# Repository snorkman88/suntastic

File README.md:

# DRAFT: Suntastic
An ultra low-power management board for meshtastic solar repeater devices.

## Overview

This repository contains the design proposal of a power management board for ultra low power embedded devices. The board features a solar charger circuit with Maximum Power Point Tracking (MPPT) for 5V solar panels, two DC-DC converters, a load switch control with adjustable hysteresis and an external Watchdog Timer.

## Why did I start this project?

### MPPT is a must
I recently started working with [Meshtastic](https://meshtastic.org/) and decided to deploy solar powered repeaters based on the WisBlock Core module that contains a RAK4631. So far it's been recommended to use this core module with any of the available base boards, however after inspecting [RAK's 19007](https://store.rakwireless.com/products/rak19007-wisblock-base-board-2nd-gen) base board, I noticed that the battery charging stage based on the [TP4054](https://www.laskakit.cz/user/related_files/tp4054.pdf) is not performing any kind of optimization to maximize the power available from the solar input.  

In contrast to linear chargers, MPPT chargers excel in extracting energy from solar panels under conditions such as partial shading, changing light angles, and fluctuating weather conditions. This adaptability is crucial for maximizing energy harvesting in real-world scenarios. By efficiently managing the charging process, MPPT helps prevent overcharging or undercharging of the accumulators in small IoT devices. This contributes to extending the overall lifespan of the battery, reducing the frequency of maintenance or battery replacement, and enhancing the device's reliability.  

### Reduce the current consumption of all the additional electronics
The recommended Wisblock base board RAK19007 contains extra electronics that are not really necessary once the RAK4631 core module has been correctly configured and flashed. This extra electronics however, do imply extra power consumption.  

As it's been empirically proven in [this thread](https://meshtastic.discourse.group/t/running-rak4631-without-the-rak19007/7021/21) once the RAK4631 core is flashed, it only needs a proper 3.3V power source to start working.  
However RAK actually recommends providing two voltage sources to the RAK4631, one that supplies power to the input of internal DC-DC buck converter and another 3.3V for the SX1262 chip. [SEE THIS POST](https://forum.rakwireless.com/t/rak4631-without-baseboard/10177/18)

### Supercapacitors as main energy storage
Another point that motivated the start of this project is the use of supercapacitors instead of conventional LiPo or LiFePo batteries. Whether supercapacitors are better than batteries for IoT devices depends on the specific requirements of the application. Here are some factors to consider:

1. Power Density:
Supercapacitors generally have higher power density than batteries. They can quickly charge and discharge, making them suitable for applications that require rapid bursts of energy. This can be advantageous in IoT devices that need to transmit data or perform periodic tasks quickly.

2. Cycle Life:
Supercapacitors often have a longer cycle life compared to batteries. Compared to batteries, they can withstand a large number of charge-discharge cycles without significant degradation in their structure even when being completely depleted and its output voltage drops down to 0V. This is beneficial for IoT devices that may need to operate for extended periods without maintenance.

3. Lifetime and Maintenance:
Supercapacitors can have a longer overall lifetime than batteries, as they do not suffer from the same degradation issues over time. They also require less maintenance since they do not have the same chemical processes that can lead to wear and tear in batteries.

4. Size and Weight:
Supercapacitors can be more compact and lighter than batteries, which is important for IoT devices with size and weight constraints. This is particularly relevant for small, portable devices or those with limited space.

5. Temperature Sensitivity:
Supercapacitors are known for their resilience to temperature variations, making them suitable for applications in harsh environments. This can be an advantage in IoT devices deployed in diverse environments where temperature fluctuations are common. Supercapacitors have a temperature range of operation og -40°C to 85°C or even higher in some cases.

6. Energy Density:
Batteries typically have higher energy density, meaning they can store more energy per unit of volume or weight. If the IoT device requires long periods of operation without recharging, a battery might be a more suitable choice.

In summary, the choice between supercapacitors and batteries for powering IoT devices depends on the specific requirements of the application. Supercapacitors may be a better choice for applications that require high power density, quick charge/discharge cycles, and long cycle life, while batteries may be preferable when higher energy density and longer operating periods without recharging are crucial. Each technology has its own strengths and limitations, and the decision should be based on the specific needs and constraints of the IoT deployment.  

### External Watchdog timers are sometimes needed
For IoT devices deployed in remote areas, the incorporation of an external watchdog timer becomes even more critical due to the challenges associated with limited accessibility and maintenance. Remote locations often entail harsh environmental conditions and restricted physical access, making it challenging to address issues promptly. The watchdog timer becomes a crucial asset in such scenarios as it autonomously monitors the device's operational state and intervenes in the case of failures. This capability ensures that even if a device experiences a software glitch or hardware malfunction, it can autonomously reset itself, mitigating potential downtime without requiring manual intervention.  

The reliability and self-correcting nature of an external watchdog timer contribute significantly to the overall resilience of IoT devices in remote deployments, enhancing their ability to function autonomously and maintain consistent operation in challenging and hard-to-reach environments.

## IMPORTANT
IMPORTANT: this board has been specifically thought to handle 5V solar panels and supercapacitors up to a voltage of 5.4V max.

## Table of Contents

- [Solar Charger Circuit](#solar-charger-circuit)
- [DC-DC Converters](#dc-dc-converters)
  - [Boost Converter](#boost-converter)
  - [Buck-Boost Converter](#buck-boost-converter)
- [UVLO - Schmitt Trigger Control](#schmitt-trigger-control)
- [External Watchdog timer](#watchdog-timer)
- [Monitoring of the voltage seen on the accumulator]()

## Solar Charger Circuit

The solar charger circuit is designed to efficiently charge an accumulator using 5V solar panels. It incorporates Maximum Power Point Tracking (MPPT) to optimize the energy harvesting from the solar panels.  

The [SPV1040](https://www.st.com/en/power-management/spv1040.html) device is a low power, low voltage, monolithic step-up converter with an input voltage range from 0.3 V to 5.5 V, capable of maximizing the energy generated by solar cells (or fuel cells), where low input voltage handling capability is extremely important. Thanks to the embedded MPPT algorithm, even under varying environmental conditions (such as irradiation, dirt, temperature) the SPV1040 offers maximum efficiency in terms of power harvested from the cells and transferred to the output. The device employs a voltage regulation loop, which fixes the charging battery voltage via a resistor divider.  

It is possible to set the maximum output current according to charging requirements by a sense resistor .

## DC-DC Converters

### Boost Converter

The first DC-DC converter that is presented is a boost converter responsible for powering the control stage and the input of the internal DC/DC converter present in the nRF52840.  
It is based on a [TPS61202](https://www.sparkfun.com/datasheets/Prototyping/tps61200.pdf) from Texas Instruments and takes variable voltage seen at the accumulator (i.e a supercapacitor) and converts it to a 5V one.  
  
This boost converter features a very low start-up voltage (0.5V) and Iq=50uA when in operation.  
For the very first version of this board, in order to save schematic and PCB design time, it would be ideal to use a ready-to-use board like the Pololu [U1V10F5](https://thepihut.com/products/pololu-5v-step-up-voltage-regulator-u1v10f5).  

For more info about this module visit [Pololu Site](https://www.pololu.com/product/2564)

### Buck-Boost Converter or LDO for obtaining 3.3V

The second voltage regulator is in charge of supplying power to the 3.3 V bus to which the SX1262 chip (present in the WisBlock RAK4631) and watchdog timer are connected.  
This regulator should only start operating after the load switch controlled by the UVLO is closed.  
It is very important to remark that clean power supplies are essential for RF transceivers to maintain optimal performance. RF signals are sensitive to electrical noise, and any disruptions in the power supply can lead to signal degradation.  

In the case a buck-boost converter (like the TPS63020) is adopted, then it could either take as an input the variable voltage from the supercapacitor or the 5V constant output coming out of the TPS61202. This approach however, necessitates more filtering of the output voltage.  

Using LDOs on the other hand, requires an input votlage higher than the one desired at the output (in this case 3.3V). Ergo, connecting its input directly to the supercapacitor is not an acceptable approach.  
Although taking 5V coming from the TPS61202 as input voltage might bring some input ripple, the PSRR of an LDO contributes to suppress it at the output.  
In the case the output of the LDO still shows some ringing at high frequencies (usually as peaks on the waveform), ferrite beads should be placed to filter the desired frequencies.  

For more detailed info about this visit this [Application Note from Analog Device - AN101](https://www.analog.com/media/en/technical-documentation/application-notes/an101f.pdf)  

or watch this video  

### Why are there two DC-DC converters?
It is desirable that the UVLO control circuit starts operating as early as possible if there is enough input power (around Vin=0.7V) and BEFORE any other electronic device. The opposite behaviour is also desired. In other words, when the input voltage coming from the accumulator decreases, the UVLO should be last part that is turned off.

Since it's expected that the control stage consumes only a few microamps when operating, the output voltage of 5V should remain steady while the accumulator (i.e: supercapacitor) continues to charge. Once the voltage seen accross the terminals of the accumulator reaches the lock-in voltage, the second converter, external watchdog timer and microcontroller will be energised.

## UVLO - Schmitt Trigger Control

The project includes an UVLO circuit with with adjustable hysteresis that enables or disables a load switch. The load connected to the switch will be the main [Buck-Boost Converter](#buck-boost-converter) that feeds power the RAK431 or another microcontroller.  

Since the supercapacitor bank I have at the moment (250F x 5.4V) already comes with an extra PCB to protect them against overvoltages higher than 5V, and for [this simulation only](https://www.falstad.com/circuit/circuitjs.html?ctz=CQAgjCAMB0l3BWEBOaBmAHAFgOyQ2AGwJhZaREiERIKQgICmAtGGAFACGIaATPfwwNeQwSCFZ0UcPHghJCJDGQqcdWXEKFkaGbPYB3Hv3DJeIXryynzkLjwTnKJJ4XHyp9MBoHQVZ9Vl+SBxdBSRvfSM+LzNjej4oQ3jjB3NEuzAEXRxCITBclBFwQoEGBnYsnOwLDCFkQgE66VsKoxwa3hxzM3zS5Nz8uIamoTsjXpK3FSd+9pq0SGsXcDdxkEHV+kdRfCSCp2LCazBi1jWNj0Vy+lvoJAA1AHsAGwAXTgBzRmSxNnNLCdTkkjICbBYrOBgXYAEpbEDnLzAxHSejkDy6W5Qe7sABOUwRRC8hWYDWkjUCdnxBTczAwxIu9B0GjxBMoNKo1jRxCiBJRRMJjRBfLJHLpt2SHIZqySnwJxwJ9NRkpJSrQjgRSvW6vM4rSyqMUos3QNxtaXQBkPWFoh1hituFf2Bp3y0MlRxOxX+SSe4BlXksyBo2PgEASKGkyB47CAA), a value of 3V was chosen for the upper limit and 1V for the lower one.  

Since it's the intention to make the supercapacitor charge up to a voltage value close to the maximum, the final version will have a lock-in voltage closer to 5V or 5.4V if I get a bank without the overvoltage protection. The lower limit of the hysterisis window will be kept at 1V.  
In order to avoid flickering of the output when the supercap voltage reaches the lock-in and -out values, an SR latch based on NOR gates will either SET (and keep it HIGH even if the input flickers) when the lock-in voltage is reached; and RESET its output when reaching the lock-out value.  

The circuit consists of two [TLV3691](https://www.ti.com/lit/ds/symlink/tlv3691.pdf?ts=1706791844150&ref_url=https%253A%252F%252Fwww.google.com%252F) nano-power comparators powered by the 5V bus.  

For the voltage references, it's yet to be defined if specific high-precision voltage references like [REF35](https://www.ti.com/lit/ds/symlink/ref35.pdf?ts=1706804680495&ref_url=https%253A%252F%252Fwww.ti.com%252Fpower-management%252Fvoltage-reference%252Fseries-voltage-reference%252Fproducts.html) will be used or simply get those reference values from a voltage divider. **Current consumption reduction is PRIORITY.**

For the latching of the output, low power [SN74AUP2G02](https://www.ti.com/lit/ds/symlink/sn74aup2g02.pdf?ts=1706885625366&ref_url=https%253A%252F%252Fwww.google.com%252F) NOR gates will be used. These gates will also be powered by the 5V bus.

The load switch will be a [TPS22917](https://www.ti.com/lit/ds/symlink/tps22917.pdf?ts=1706648579344&ref_url=https%253A%252F%252Fwww.google.com%252F).

In summary this circuit makes sure the embedded device stays de-energised until the supercapacitor is fully charged.

## Watchdog timer  

If for any unforeseen reason, the voltage supplied to the core module drops low enough that the device shuts down or to a level that causes a brown-out, it may not be able to resume its normal operation by itself without external intervention (manually or by automation) that either removes and reconnects the voltage supply or issues a reset.  

An external watchdog timer will issue a reset in case of a software bug/glitch or brownout will be a [TPL5010](https://www.ti.com/lit/ds/symlink/tpl5010.pdf?ts=1706954677109&ref_url=https%253A%252F%252Fwww.google.com%252F) from Texas Instrument.  

The DONE signal resets the counter of the watchdog only. If the DONE signal is received when the WAKE is still high, the WAKE will go low as soon as the DONE is recognized.

For this feature to be fully functional, two GPIO pins and **CHANGES IN THE CORE MODULE FIRMWARE ARE NEEDED** to monitor the WAKE signal and generate a DONE pulse to reset the counter of the  WDT.  
Images taken from the datasheet.  

## Monitoring the current voltage on the supercapacitor
Also mentioned in [this thread](https://meshtastic.discourse.group/t/running-rak4631-without-the-rak19007/7021/21). A voltage divider must be connected to Pin40 (P0.05/AIN3) of the RAK4631.  

**CHANGES IN THE CORE MODULE FIRMWARE ARE NEEDED TOO** in order to properly reflect the current voltage value on the supercapacitor based on the resistors ratio from the voltage divider.

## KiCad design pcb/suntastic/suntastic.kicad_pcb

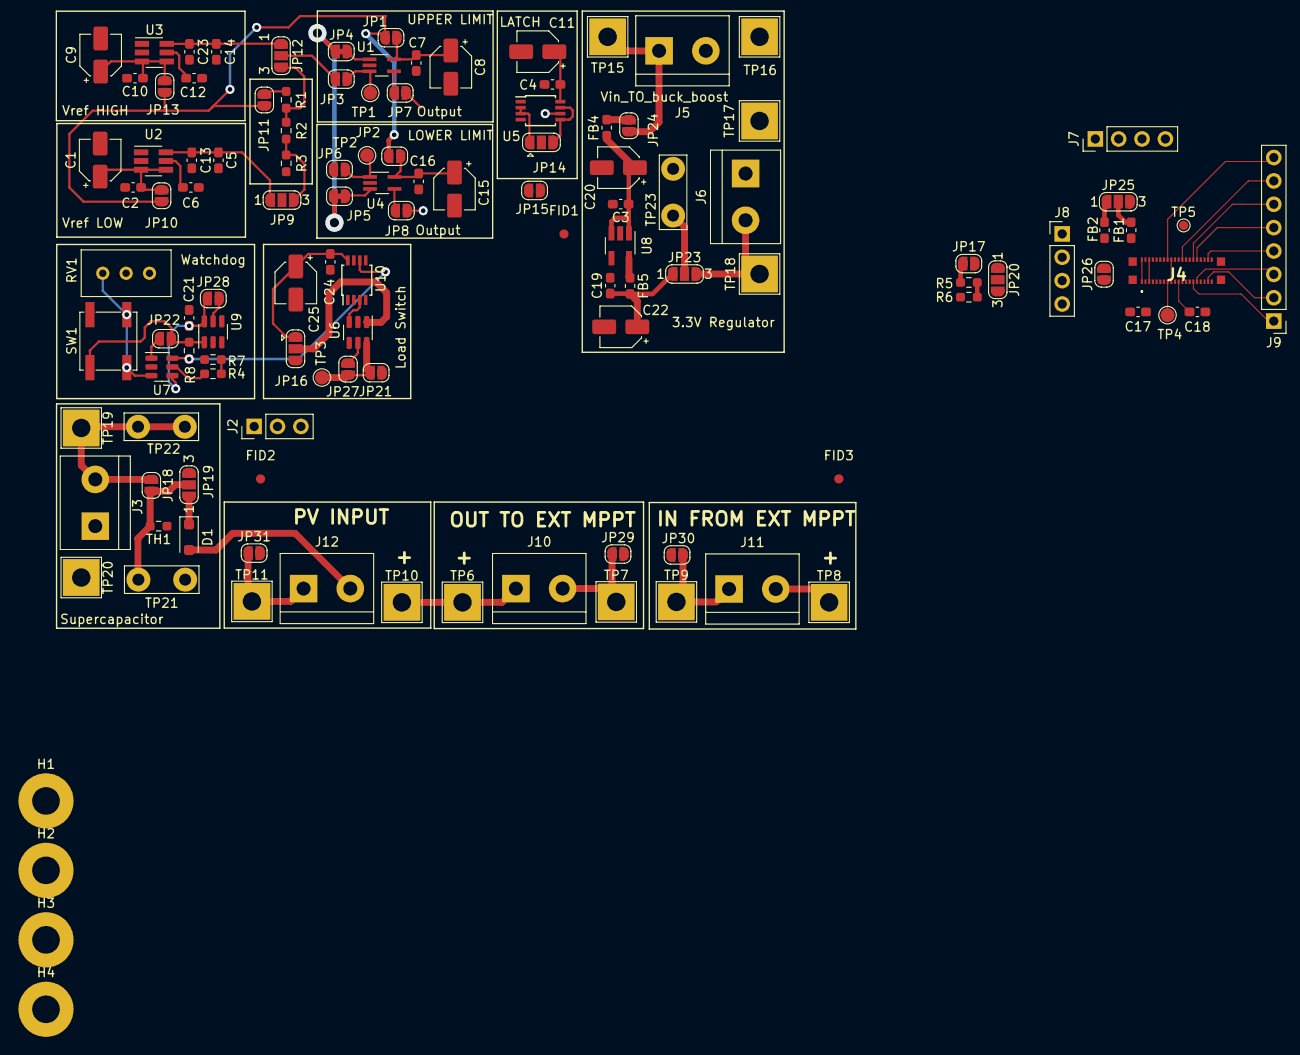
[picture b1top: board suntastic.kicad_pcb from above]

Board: 2 copper layers, 120 parts (0 on the bottom side), 78 nets.

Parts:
C1, C9: 2.2uF; CP_Elec_4x5.4
C2, C4, C5, C6, C7, C10, C12, C14, C16, C17, C18, C24: 0.1uF; C_0603_1608Metric_Pad1.08x0.95mm_HandSolder
C3, C13, C19, C21, C23: 1uF; C_0603_1608Metric_Pad1.08x0.95mm_HandSolder
C8, C15: 4.7uF; CP_Elec_4x5.4
C11, C25: 1uF; CP_Elec_4x4.5
C20, C22: 10u; CP_Elec_4x4.5
D1: PMEG10020ELR; D_SOD-123F
FB1, FB2, FB4, FB5: FerriteBead; L_0603_1608Metric_Pad1.05x0.95mm_HandSolder
FID1, FID2, FID3: Fiducial; Fiducial_1mm_Mask3mm
H1, H2, H3, H4: MountingHole; MountingHole_3mm_Pad
J2: Pololu U1V10F5; PinHeader_1x03_P2.54mm_Vertical
J3: Supercap IN; TerminalBlock_bornier-2_P5.08mm
J4: FBB04004-F40S1003K6M; FBB04004F40S1003K6M
J5: Vin_TO_buck_boost; TerminalBlock_bornier-2_P5.08mm
J6: Vout_FROM_buck_boost; TerminalBlock_bornier-2_P5.08mm
J7, J8: Conn_01x04_Pin; PinHeader_1x04_P2.54mm_Vertical
J9: Conn_01x08_Pin; PinHeader_1x08_P2.54mm_Vertical
J10: OUT TO EXT MPPT; TerminalBlock_bornier-2_P5.08mm
J11: INPUT FROM EXT MPPT; TerminalBlock_bornier-2_P5.08mm
J12: PV IN; TerminalBlock_bornier-2_P5.08mm
JP1, JP2, JP3, JP6, JP7, JP8, JP10, JP11, JP13, JP15, JP17, JP21, JP22, JP24, JP26, JP27, JP28: SolderJumper_2_Open; SolderJumper-2_P1.3mm_Open_RoundedPad1.0x1.5mm
JP4, JP5: SolderJumper_2_Bridged; SolderJumper-2_P1.3mm_Bridged_RoundedPad1.0x1.5mm
JP9, JP12, JP19, JP20, JP23, JP25: SolderJumper_3_Open; SolderJumper-3_P1.3mm_Open_RoundedPad1.0x1.5mm_NumberLabels
JP14, JP16: SolderJumper_3_Open; SolderJumper-3_P1.3mm_Open_RoundedPad1.0x1.5mm
JP18, JP29, JP30, JP31: Jumper_2_Open; SolderJumper-2_P1.3mm_Open_RoundedPad1.0x1.5mm
R1, R7: 3.3M; R_0603_1608Metric_Pad0.98x0.95mm_HandSolder
R2, R6: 9.3M; R_0603_1608Metric_Pad0.98x0.95mm_HandSolder
R3: 3.9M; R_0603_1608Metric_Pad0.98x0.95mm_HandSolder
R4: 1.8M; R_0603_1608Metric_Pad0.98x0.95mm_HandSolder
R5: 5.6M; R_0603_1608Metric_Pad0.98x0.95mm_HandSolder
R8: R; R_0603_1608Metric_Pad0.98x0.95mm_HandSolder
RV1: 120k; Potentiometer_Bourns_3296W_Vertical
SW1: EVP-BF6C1A000; SW_SPST_EVPBF
TH1: Thermistor_PTC; R_0603_1608Metric_Pad0.98x0.95mm_HandSolder
TP1: Vref_high; TestPoint_Pad_D1.5mm
TP2: Vref_low; TestPoint_Pad_D1.5mm
TP3: Vout_switch; TestPoint_Pad_D1.5mm
TP4: LED2; TestPoint_Pad_D1.5mm
TP5: LED1; TestPoint_Pad_D1.0mm
TP6: PV_TO_MPPT; TestPoint_THTPad_4.0x4.0mm_Drill2.0mm
TP7: GND_TO_MPPT; TestPoint_THTPad_4.0x4.0mm_Drill2.0mm
TP8: OUT_FROM_MPPT; TestPoint_THTPad_4.0x4.0mm_Drill2.0mm
TP9: GND_FROM_MPPT; TestPoint_THTPad_4.0x4.0mm_Drill2.0mm
TP10: PV_VIN; TestPoint_THTPad_4.0x4.0mm_Drill2.0mm
TP11: PV_GND; TestPoint_THTPad_4.0x4.0mm_Drill2.0mm
TP15, TP16, TP17, TP18: TestPoint; TestPoint_THTPad_4.0x4.0mm_Drill2.0mm
TP19: SC_VIN; TestPoint_THTPad_4.0x4.0mm_Drill2.0mm
TP20: SC_GND; TestPoint_THTPad_4.0x4.0mm_Drill2.0mm
TP21, TP22: TestPoint; TestPoint_Bridge_Pitch5.08mm_Drill1.3mm
TP23: 3.3V; TestPoint_Bridge_Pitch5.08mm_Drill1.3mm
U1, U4: TLV3691IDCKR; SOT-353_SC-70-5_Handsoldering
U2: REF35102QDBVR; SOT-23-6_Handsoldering
U3: REF35409QDBVR; SOT-23-6_Handsoldering
U5: TC7WH02FU_LJCT; TSSOP-8_3x3mm_P0.65mm
U6, U9: TPS22917DBV; SOT-23-6
U7: TPL5010; SOT-23-6
U8: XC6220B331MR; SOT-23-5_HandSoldering
U10: TC7WH08FK_LJCT; TSSOP-8_3x3mm_P0.65mm

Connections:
3.3V: FB2.1, JP23.2 (C), JP25.1 (A), TP23.1
/Sheetname: UVLO with latched output/NOR_1_OUT: JP14.3 (B), U5.5, U5.7
/Sheetname: UVLO with latched output/NOR_2_OUT: JP14.1 (A), U5.2, U5.3
/Sheetname: UVLO with latched output/RESET: JP7.2 (B), U5.1
/Sheetname: UVLO with latched output/SET: JP8.2 (B), U5.6
/WisBlock Core Module - RAK4631/3V3: FB2.2, J4.5, J4.6, JP26.2 (B)
/WisBlock Core Module - RAK4631/AIN0: C18.1, J4.21, JP20.3 (B)
/WisBlock Core Module - RAK4631/AIN1: J4.22, JP20.1 (A)
/WisBlock Core Module - RAK4631/BOOT0: J4.23, J7.1
/WisBlock Core Module - RAK4631/IO1: J4.29, J9.1
/WisBlock Core Module - RAK4631/IO2: J4.30, J9.6
/WisBlock Core Module - RAK4631/IO3: J4.31, J9.3
/WisBlock Core Module - RAK4631/IO4: J4.32, J9.5
/WisBlock Core Module - RAK4631/IO5: J4.37, J9.2
/WisBlock Core Module - RAK4631/IO6: J4.38, J9.4
/WisBlock Core Module - RAK4631/IO7: J4.24, J9.7
/WisBlock Core Module - RAK4631/IO8: J4.16, J9.8
/WisBlock Core Module - RAK4631/RXD0: J4.12, J8.4
/WisBlock Core Module - RAK4631/RXD1: J4.34, J7.4
/WisBlock Core Module - RAK4631/TXD0: J4.11, J8.3
/WisBlock Core Module - RAK4631/TXD1: J4.33, J7.3
/WisBlock Core Module - RAK4631/VBAT_nRF: FB1.2, J4.1, J4.2
/WisBlock Core Module - RAK4631/VDD_nRF: J4.17, J4.18, JP26.1 (A)
/WisBlock Core Module - RAK4631/Vsupercap: JP20.2 (C), R5.2, R6.1
GND: C1.2, C2.2, C3.2, C4.2, C5.2, C6.2, C7.2, C8.2, C9.2, C10.2, C11.2, C12.2, C13.2, C14.2, C15.2, C16.2, C17.2, C18.2, C19.2, C20.2, C21.2, C22.2, C23.2, C24.2, C25.2, J2.2, J3.1, J4.3, J4.4, J4.39, J4.40, J4.MP1, J4.MP2, J4.MP3, J4.MP4, J5.2, J6.1, J7.2, J8.2, JP29.2 (B), JP30.2 (B), JP31.2 (B), R3.2, R6.2, R7.2, RV1.2, RV1.3, TP16.1, TP17.1, TP20.1, U1.2 (GND), U2.1 (GND), U2.2 (GND), U3.1 (GND), U3.2 (GND), U4.2 (GND), U5.4, U6.2 (GND), U7.2 (GND), U8.2 (GND), U9.2 (GND), U10.1 (1A), U10.2 (1B), U10.4 (GND)
GPIO_WAKE: R4.2, R7.1
LOAD_SWITCH_CTRL: JP14.2 (C), JP15.1 (A)
MPPT_OUT: J11.2, JP19.3 (B), TP8.1
unnamed: D1.1 (K), JP19.1 (A)
unnamed: J3.2, JP18.1 (A), TP19.1, TP22.1
unnamed: J4.14, TP5.1
unnamed: J4.15, TP4.1
unnamed: J6.2, JP23.3 (B), TP18.1
unnamed: J10.2, JP29.1 (A), TP7.1
unnamed: J11.1, JP30.1 (A), TP9.1
unnamed: J12.1, JP31.1 (A), TP11.1
unnamed: C7.1, C8.1, JP1.1 (A), U1.5 (VCC)
unnamed: C15.1, C16.1, JP2.1 (A), U4.5 (VCC)
unnamed: JP3.2 (B), TP1.1, U1.3 (IN-)
unnamed: JP4.2 (B), U1.1 (IN+)
unnamed: JP5.2 (B), U4.3 (IN-)
unnamed: JP6.2 (B), TP2.1, U4.1 (IN+)
unnamed: JP7.1 (A), U1.4 (OUT)
unnamed: JP8.1 (A), U4.4 (OUT)
unnamed: C5.1, C13.1, JP9.1 (A), U2.6 (VREF)
unnamed: JP9.3 (B), R2.2, R3.1
unnamed: C1.1, C2.1, JP10.2 (B), U2.3 (EN), U2.4 (VIN)
unnamed: JP11.2 (B), R1.1
unnamed: C14.1, C23.1, JP12.1 (A), U3.6 (VREF)
unnamed: JP12.3 (B), R1.2, R2.1
unnamed: C9.1, C10.1, JP13.2 (B), U3.3 (EN), U3.4 (VIN)
unnamed: JP15.2 (B), U10.5 (2A)
unnamed: JP16.2 (C), U6.1 (VIN)
unnamed: JP17.2 (B), R5.1
unnamed: JP18.2 (B), JP19.2 (C), TH1.2, TP21.1
unnamed: JP21.1 (A), JP27.2 (B), TP3.1, U6.6 (VOUT)
unnamed: JP22.2 (B), U7.1 (VDD)
unnamed: C19.1, C22.1, FB5.2, JP23.1 (A)
unnamed: FB4.1, JP24.2 (B)
unnamed: FB1.1, JP25.2 (C)
unnamed: JP27.1 (A), U6.5 (QOD)
unnamed: C21.1, JP28.1 (A), U7.4 (DONE), U9.6 (VOUT)
unnamed: JP28.2 (B), U9.5 (QOD)
unnamed: C6.1, U2.5 (NR)
unnamed: C12.1, U3.5 (NR)
unnamed: RV1.1, SW1.1, U7.3 (DELAY/M_RST)
unnamed: R4.1, U7.5 (WAKE)
unnamed: C3.1, C20.1, FB4.2, U8.1 (VIN), U8.3 (CE)
unnamed: FB5.1, U8.5 (VOUT)
unnamed: U6.3 (ON), U10.3 (OUT_2)
PV_+: D1.2 (A), J10.1, J12.2, TP6.1, TP10.1
RST_SIGNAL: R8.2, U7.6 (~RST), U10.6 (2B)
V_boost_uvlo: C4.1, C11.1, C24.1, C25.1, J2.3, JP1.2 (B), JP2.2 (B), JP10.1 (A), JP11.1 (A), JP13.1 (A), JP16.1 (A), JP22.1 (A), JP25.3 (B), R8.1, SW1.2, U5.8, U9.1 (VIN), U10.8 (VDD)
V_supercap: J2.1, JP4.1 (A), JP5.1 (A), JP16.3 (B), JP17.1 (A), TH1.1
Vin_buck_boost: J5.1, JP21.2 (B), JP24.1 (A), TP15.1
Vref_high: JP3.1 (A), JP12.2 (C)
Vref_low: JP6.1 (A), JP9.2 (C)
nRF_RESET: C17.1, J4.13

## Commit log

2024-02-04 Add block diagram
2024-02-04 Fix background color
2024-02-04 Add fixed svg
2024-02-05 Add screenshots
2024-02-05 Add tplimage
2024-02-05 More pictures
2024-02-08 Update boost circuit
2024-02-09 Update boost circuit for UVLO
2024-02-09 Add UVLO and latch schematics
2024-02-09 Rename sheet
2024-02-09 Update block diagram
2024-02-09 Fix block diagram and path
2024-02-10 Add load switch and RAK connector
2024-02-10 Add more doccstrings
2024-02-14 add wdt
2024-02-14 Add two alternatives to obtain 3.3V for the SX chip
2024-02-16 Update footprints
2024-02-17 Update more footprints and start with PCB
2024-02-19 Rework watchdog
2024-02-19 Add screw terminals for external MPPT module and PV input
